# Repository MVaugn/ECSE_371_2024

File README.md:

# ECSE_371_2024
Applied Circuit Design, as taught in Spring of 2024. The last Larry Lab featuring Larry Sears himself!

This page and its contents are for reference only. Learn all you can from these examples, but PLEASE design your own circuits. No cheating >:(

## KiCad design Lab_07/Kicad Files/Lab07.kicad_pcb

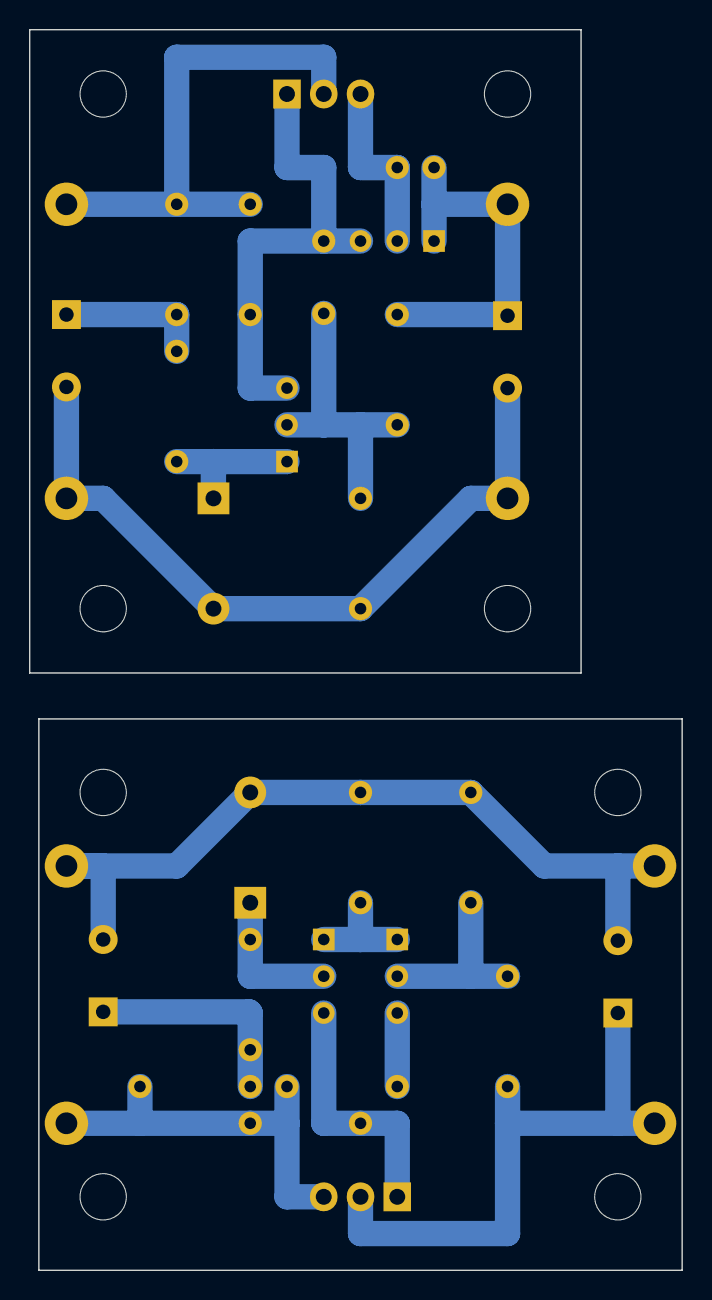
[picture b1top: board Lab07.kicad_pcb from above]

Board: 2 copper layers, 45.1 x 85.7 mm, 34 parts (0 on the bottom side), 16 nets.

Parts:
C101: 22uF; CP_Radial_D10.0mm_P5.00mm
C102: 0.01uF; C_Disc_D10.0mm_W2.5mm_P5.00mm
C103, C302: 100uF; CP_Radial_D10.0mm_P5.00mm
C301: 220uF; CP_Radial_D10.0mm_P5.00mm
D101, D301: 6.2V; D_DO-41_SOD81_P7.62mm_Horizontal
J101, J102, J301, J302: Conn_01x01_Socket; TestPoint_Loop_D2.54mm_Drill1.5mm_Beaded
J103, J304: 0; TestPoint_Loop_D2.54mm_Drill1.5mm_Beaded
J104, J303: Output_Terminal; TestPoint_Loop_D2.54mm_Drill1.5mm_Beaded
Q101, Q103, Q301, Q303: NPN; TO-92L_Inline_Wide
Q102: TIP102; TO-220-3_Vertical
Q302: PMOS; TO-220-3_Vertical
R101, R103, R301, R302: 1K; R_Axial_DIN0207_L6.3mm_D2.5mm_P7.62mm_Horizontal
R102, R106: 2K2; R_Axial_DIN0207_L6.3mm_D2.5mm_P7.62mm_Horizontal
R104: 390m; R_Axial_DIN0207_L6.3mm_D2.5mm_P2.54mm_Vertical
R105: 680R; R_Axial_DIN0207_L6.3mm_D2.5mm_P7.62mm_Horizontal
R303, R304: 100K; R_Axial_DIN0207_L6.3mm_D2.5mm_P7.62mm_Horizontal
R305: 8K2; R_Axial_DIN0207_L6.3mm_D2.5mm_P7.62mm_Horizontal
R306: 1K5; R_Axial_DIN0207_L6.3mm_D2.5mm_P7.62mm_Horizontal
R307: 4K7; R_Axial_DIN0207_L6.3mm_D2.5mm_P7.62mm_Horizontal

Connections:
/Vin_1: J101.1, Q102.2 (C), R101.1, R102.1
/Vin_3: J301.1, Q302.3 (S), R301.1, R303.1, R304.1
/Vout_1: C103.1, J103.1 (In), Q103.1 (E), R104.2, R105.1
/Vout_3: C302.1, J303.1 (In), Q302.2 (D), R306.1
GND: C101.2, C103.2, C301.2, C302.2, D101.2 (A), D301.2 (A), J102.1, J104.1 (In), J302.1, J304.1 (In), R106.2, R305.2, R307.2
unnamed: C101.1, R101.2, R103.1
unnamed: C301.1, R301.2, R302.1
unnamed: D101.1 (K), Q101.1 (E), R103.2
unnamed: D301.1 (K), Q301.2 (B), R302.2
unnamed: C102.2, Q101.2 (B), R105.2, R106.1
unnamed: C102.1, Q101.3 (C), Q102.1 (B), Q103.3 (C), R102.2
unnamed: Q102.3 (E), Q103.2 (B), R104.1
unnamed: Q301.3 (C), Q302.1 (G), R304.2
unnamed: Q301.1 (E), Q303.1 (E), R305.1
unnamed: Q303.2 (B), R306.2, R307.1
unnamed: Q303.3 (C), R303.2

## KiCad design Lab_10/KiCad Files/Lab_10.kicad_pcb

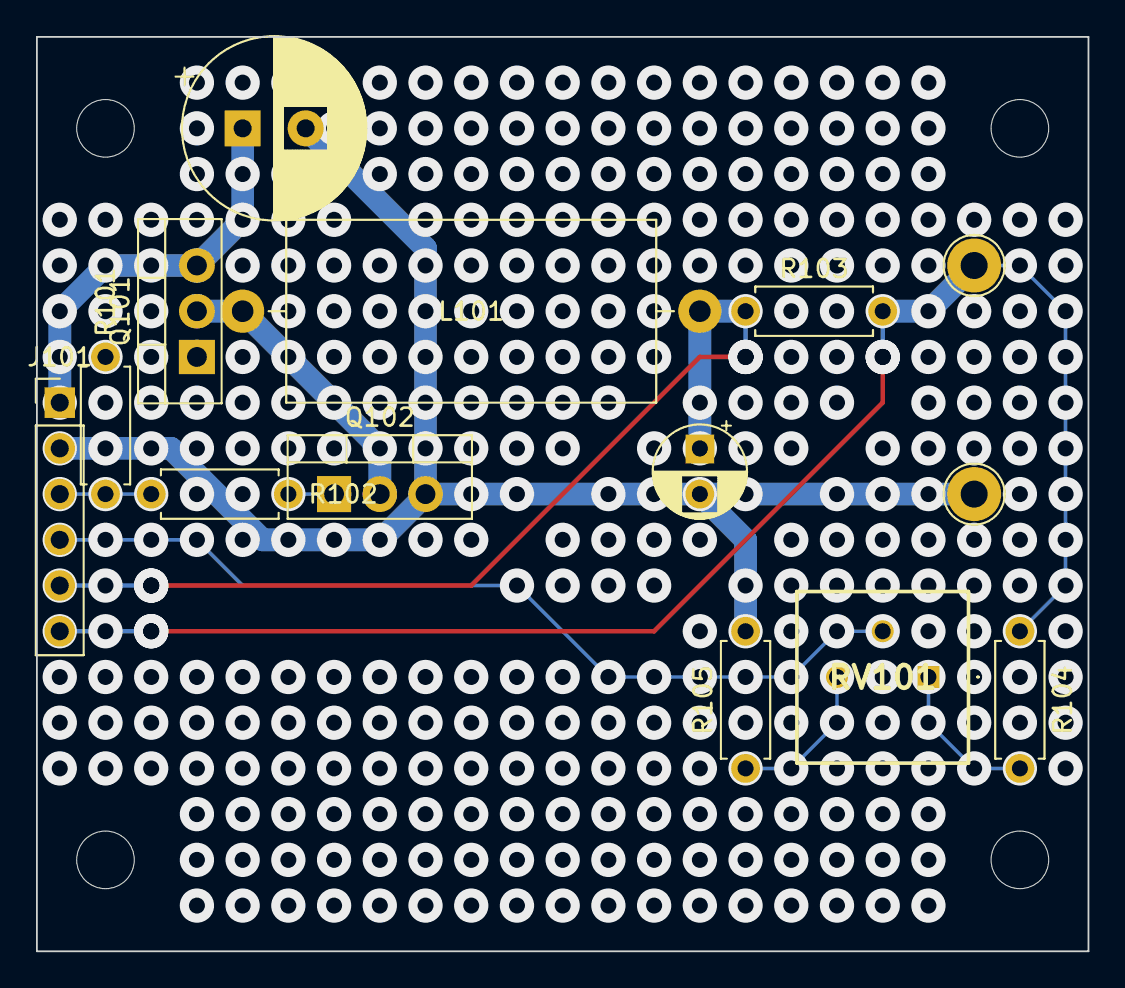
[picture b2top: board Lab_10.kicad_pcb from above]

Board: 2 copper layers, 58.4 x 50.8 mm, 14 parts (0 on the bottom side), 11 nets.

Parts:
C101: 100uF; CP_Radial_D10.0mm_P3.50mm
C102: 10uF; CP_Radial_D5.0mm_P2.50mm
J101: Conn_01x06_Socket; PinHeader_1x06_P2.54mm_Vertical
J102, J103: Output_Terminal; TestPoint_Loop_D2.54mm_Drill1.5mm_Beaded
L101: 820uH; L_Axial_L20.3mm_D12.7mm_P25.40mm_Horizontal_Vishay_IHA-201
Q101: IRF9Z24; TO-220-3_Vertical
Q102: IRF530; TO-220-3_Vertical
R101, R102: 100R; R_Axial_DIN0207_L6.3mm_D2.5mm_P7.62mm_Horizontal
R103: 0.12R; R_Axial_DIN0207_L6.3mm_D2.5mm_P7.62mm_Horizontal
R104: 1K; R_Axial_DIN0207_L6.3mm_D2.5mm_P7.62mm_Horizontal
R105: 27K; R_Axial_DIN0207_L6.3mm_D2.5mm_P7.62mm_Horizontal
RV101: 50K; 3386P1503

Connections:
/GateDrive: J101.3, R101.2, R102.1
/Vfdbk: J101.4, RV101.2
/Vs+: C102.1, J101.5, L101.2, R103.1
/Vs-: J101.6, J103.1 (In), R103.2, R104.1
unnamed: L101.1, Q101.2 (D), Q102.2 (D)
unnamed: Q101.1 (G), R101.1
unnamed: Q102.1 (G), R102.2
unnamed: R104.2, RV101.1
unnamed: R105.1, RV101.3
PGND: C101.2, C102.2, J101.2, J102.1 (In), Q102.3 (S), R105.2
V_Supply: C101.1, J101.1, Q101.3 (S)

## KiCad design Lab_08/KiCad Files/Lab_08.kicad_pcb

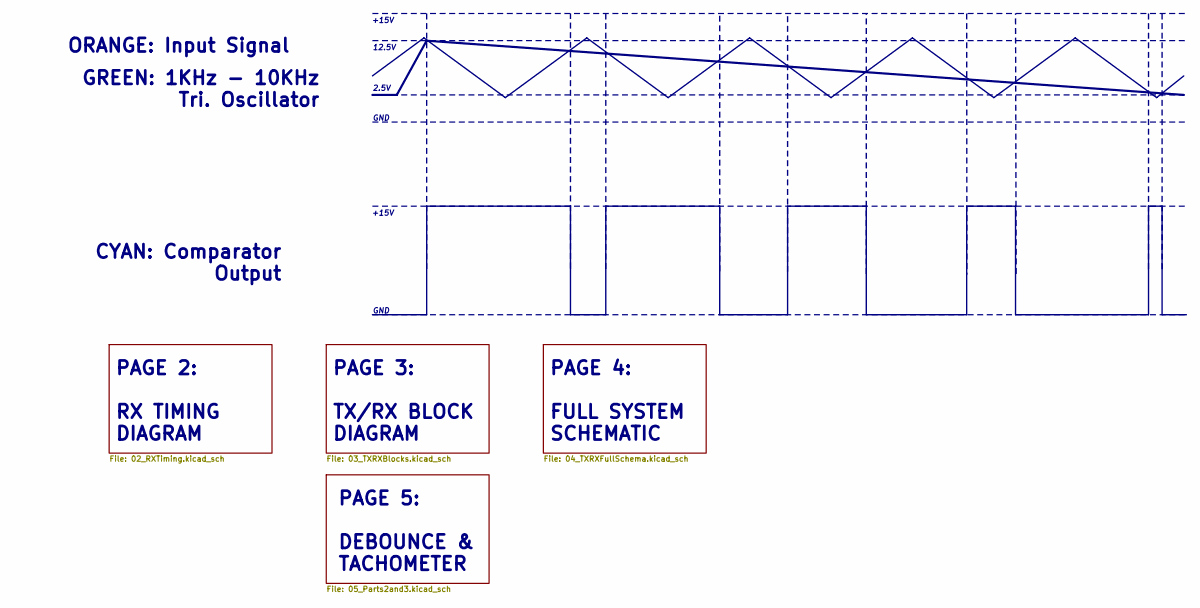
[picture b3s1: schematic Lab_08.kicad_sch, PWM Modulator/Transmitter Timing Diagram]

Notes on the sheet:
PAGE 4: FULL SYSTEM SCHEMATIC
ORANGE: Input Signal
2.5V
GREEN: 1KHz - 10KHz Tri. Oscillator
PAGE 3: TX/RX BLOCK DIAGRAM
CYAN: Comparator Output
+15V
12.5V
PAGE 2: RX TIMING DIAGRAM
GND
PAGE 5: DEBOUNCE & TACHOMETER

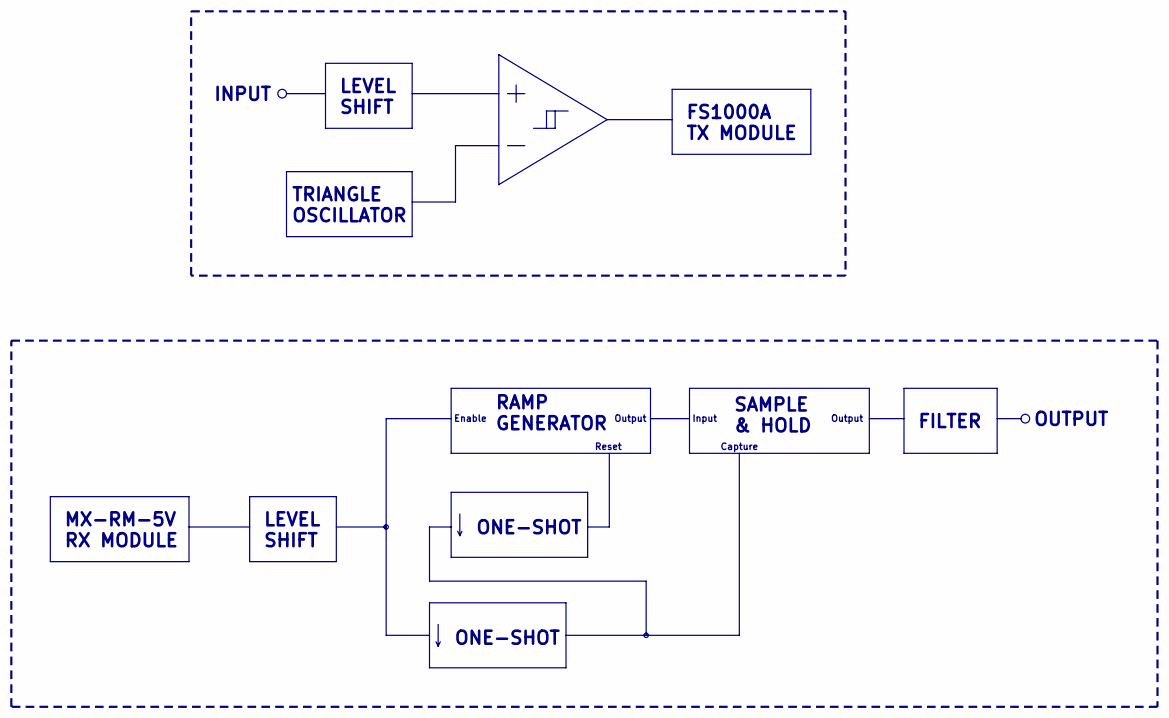
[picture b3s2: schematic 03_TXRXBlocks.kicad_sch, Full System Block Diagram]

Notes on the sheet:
FILTER
Output
Capture
RAMP GENERATOR
ONE-SHOT
LEVEL SHIFT
FS1000A TX MODULE
MX-RM-5V RX MODULE
TRIANGLE OSCILLATOR
Reset
Enable
OUTPUT
INPUT
SAMPLE & HOLD
Input

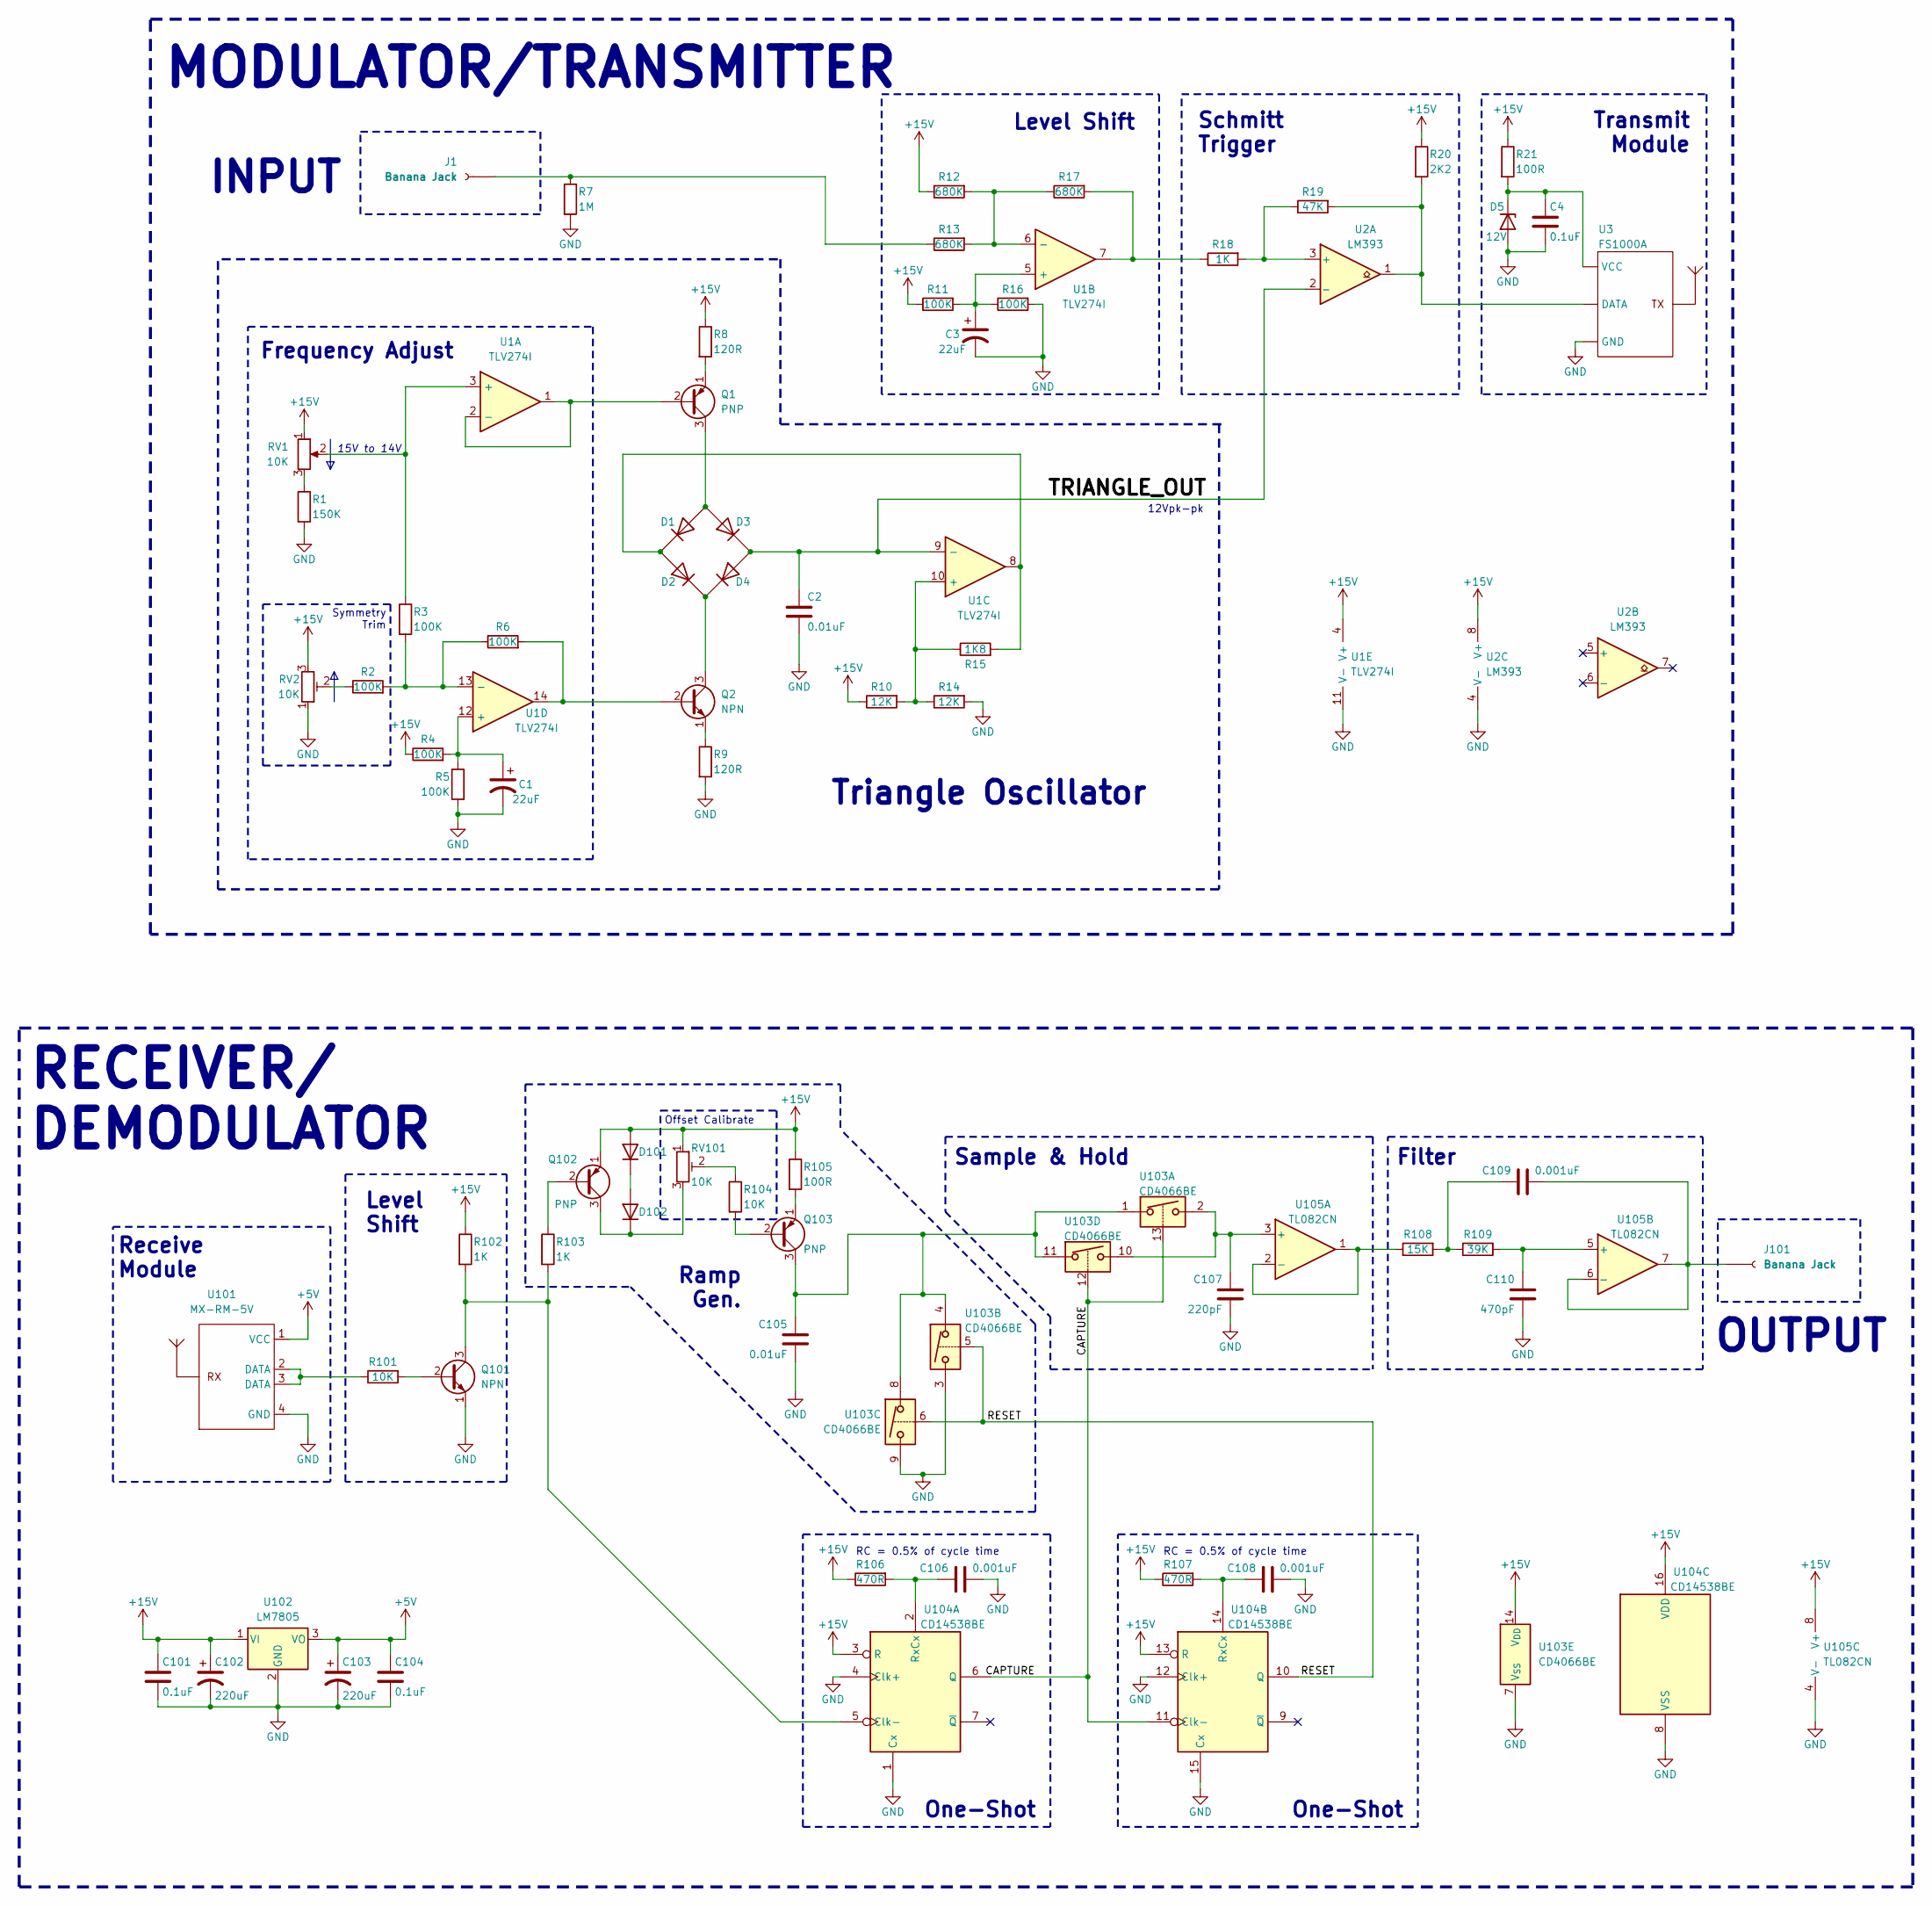
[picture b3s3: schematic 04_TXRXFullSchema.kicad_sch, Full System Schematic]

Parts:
C1, C3: 22uF; CP_Radial_D6.3mm_P2.50mm
C2, C105: 0.01uF; C_Disc_D3.0mm_W1.6mm_P2.50mm
C4, C101, C104: 0.1uF; C_Rect_L11.0mm_W2.8mm_P10.00mm_MKT
C102, C103: 220uF; CP_Radial_D8.0mm_P5.00mm
C106, C108, C109: 0.001uF; C_Disc_D3.0mm_W1.6mm_P2.50mm
C107: 220pF; C_Disc_D3.0mm_W1.6mm_P2.50mm
C110: 470pF; C_Disc_D3.0mm_W1.6mm_P2.50mm
D1, D2, D3, D4: D_A-405_P7.62mm_Horizontal
D5: 12V; D_A-405_P7.62mm_Horizontal
D101, D102: D; D_A-405_P7.62mm_Horizontal
J1, J101: Banana Jack
Q1, Q102, Q103: PNP; TO-92_Inline_Wide
Q2, Q101: NPN; TO-92_Inline_Wide
R1: 150K; R_Axial_DIN0207_L6.3mm_D2.5mm_P10.16mm_Horizontal
R2, R5, R11: 100K; R_Axial_DIN0207_L6.3mm_D2.5mm_P7.62mm_Horizontal
R3, R4, R16: 100K; R_Axial_DIN0207_L6.3mm_D2.5mm_P10.16mm_Horizontal
R6: 100K; R_Axial_DIN0207_L6.3mm_D2.5mm_P5.08mm_Vertical
R7: 1M; R_Axial_DIN0207_L6.3mm_D2.5mm_P10.16mm_Horizontal
R8, R9: 120R; R_Axial_DIN0207_L6.3mm_D2.5mm_P7.62mm_Horizontal
R10, R14: 12K; R_Axial_DIN0207_L6.3mm_D2.5mm_P10.16mm_Horizontal
R12, R13: 680K; R_Axial_DIN0207_L6.3mm_D2.5mm_P7.62mm_Horizontal
R15: 1K8; R_Axial_DIN0207_L6.3mm_D2.5mm_P5.08mm_Vertical
R17: 680K; R_Axial_DIN0207_L6.3mm_D2.5mm_P2.54mm_Vertical
R18, R102, R103: 1K; R_Axial_DIN0207_L6.3mm_D2.5mm_P7.62mm_Horizontal
R19: 47K; R_Axial_DIN0207_L6.3mm_D2.5mm_P5.08mm_Vertical
R20: 2K2; R_Axial_DIN0207_L6.3mm_D2.5mm_P7.62mm_Horizontal
R21, R105: 100R; R_Axial_DIN0207_L6.3mm_D2.5mm_P7.62mm_Horizontal
R101, R104: 10K; R_Axial_DIN0207_L6.3mm_D2.5mm_P7.62mm_Horizontal
R106: 470R; R_Axial_DIN0207_L6.3mm_D2.5mm_P7.62mm_Horizontal
R107: 470R; R_Axial_DIN0207_L6.3mm_D2.5mm_P10.16mm_Horizontal
R108: 15K; R_Axial_DIN0207_L6.3mm_D2.5mm_P7.62mm_Horizontal
R109: 39K; R_Axial_DIN0207_L6.3mm_D2.5mm_P7.62mm_Horizontal
RV1, RV2, RV101: 10K; Potentiometer_ACP_CA9-V10_Vertical
U1: TLV274I; DIP-14_W7.62mm
U2: LM393; DIP-8_W7.62mm
U3: FS1000A; PinHeader_1x03_P2.54mm_Vertical
U101: MX-RM-5V; PinHeader_1x04_P2.54mm_Vertical
U102: LM7805; TO-220-3_Vertical
U103: CD4066BE; DIP-14_W7.62mm
U104: CD14538BE; DIP-16_W7.62mm
U105: TL082CN; DIP-8_W7.62mm

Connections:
+5V: C103.1, C104.1, U101.1 (VCC), U102.3 (VO)
+15V: C101.1, C102.1, D101.2 (A), Q102.1 (E), R4.1, R8.1, R10.1, R11.1, R12.1, R20.1, R21.1, R102.1, R105.1, R106.1, R107.1, RV1.1, RV2.3, RV101.1, U1.4 (V+), U2.8 (V+), U102.1 (VI), U103.14 (V_{DD}), U104.3 (R), U104.13 (R), U104.16 (VDD), U105.8 (V+)
/Full Schematic/CAPTURE: U103.12, U103.13, U104.6 (Q), U104.11 (Clk-)
/Full Schematic/RESET: U103.5, U103.6, U104.10 (Q)
/Full Schematic/TRIANGLE_OUT: C2.1, D3.1 (K), D4.2 (A), U1.9 (-), U2.2 (-)
GND: C1.2, C2.2, C3.2, C4.2, C101.2, C102.2, C103.2, C104.2, C105.2, C106.1, C107.2, C108.1, C110.2, D5.2 (A), Q101.1 (E), R1.2, R5.2, R7.2, R9.2, R14.2, R16.2, RV2.1, U1.11 (V-), U2.4 (V-), U3.3 (GND), U101.4 (GND), U102.2 (GND), U103.3, U103.7 (V_{SS}), U103.9, U104.1 (Cx), U104.4 (Clk+), U104.8 (VSS), U104.12 (Clk+), U104.15 (Cx), U105.4 (V-)
unnamed: C109.2, R108.2, R109.1
unnamed: D1.2 (A), D3.2 (A), Q1.3 (C)
unnamed: D1.1 (K), D2.2 (A), R15.2, U1.8
unnamed: D2.1 (K), D4.1 (K), Q2.3 (C)
unnamed: C4.1, D5.1 (K), R21.2, U3.2 (VCC)
unnamed: D101.1 (K), D102.2 (A)
unnamed: D102.1 (K), Q102.3 (C), RV101.3
unnamed: Q1.2 (B), U1.1, U1.2 (-)
unnamed: Q1.1 (E), R8.2
unnamed: Q2.2 (B), R6.2, U1.14
unnamed: Q2.1 (E), R9.1
unnamed: Q101.2 (B), R101.2
unnamed: Q101.3 (C), R102.2, R103.2, U104.5 (Clk-)
unnamed: Q102.2 (B), R103.1
unnamed: Q103.2 (B), R104.2
unnamed: C105.1, Q103.3 (C), U103.1, U103.4, U103.8, U103.11
unnamed: Q103.1 (E), R105.2
unnamed: R1.1, RV1.3
unnamed: R2.1, RV2.2
unnamed: R7.1, R13.1
unnamed: R17.2, R18.1, U1.7
unnamed: R101.1, U101.2 (DATA), U101.3 (DATA)
unnamed: R104.1, RV101.2
unnamed: R3.1, RV1.2, U1.3 (+)
unnamed: C3.1, R11.2, R16.1, U1.5 (+)
unnamed: R12.2, R13.2, R17.1, U1.6 (-)
unnamed: R10.2, R14.1, R15.1, U1.10 (+)
unnamed: C1.1, R4.2, R5.1, U1.12 (+)
unnamed: R2.2, R3.2, R6.1, U1.13 (-)
unnamed: R18.2, R19.1, U2.3 (+)
unnamed: R19.2, R20.2, U2.1, U3.1 (DATA)
unnamed: C106.2, R106.2, U104.2 (RxCx)
unnamed: C108.2, R107.2, U104.14 (RxCx)
unnamed: C107.1, U103.2, U103.10, U105.3 (+)
unnamed: R108.1, U105.1, U105.2 (-)
unnamed: C110.1, R109.2, U105.5 (+)
unnamed: C109.1, J101.1, U105.6 (-), U105.7

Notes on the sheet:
Level Shift
RECEIVER/ DEMODULATOR
INPUT
Triangle Oscillator
Schmitt Trigger
One-Shot
Sample & Hold
Ramp Gen.
OUTPUT
12Vpk-pk
MODULATOR/TRANSMITTER
Frequency Adjust
Receive Module
15V to 14V
RC = 0.5% of cycle time
Symmetry Trim
Transmit Module
Level Shift
Offset Calibrate
Filter

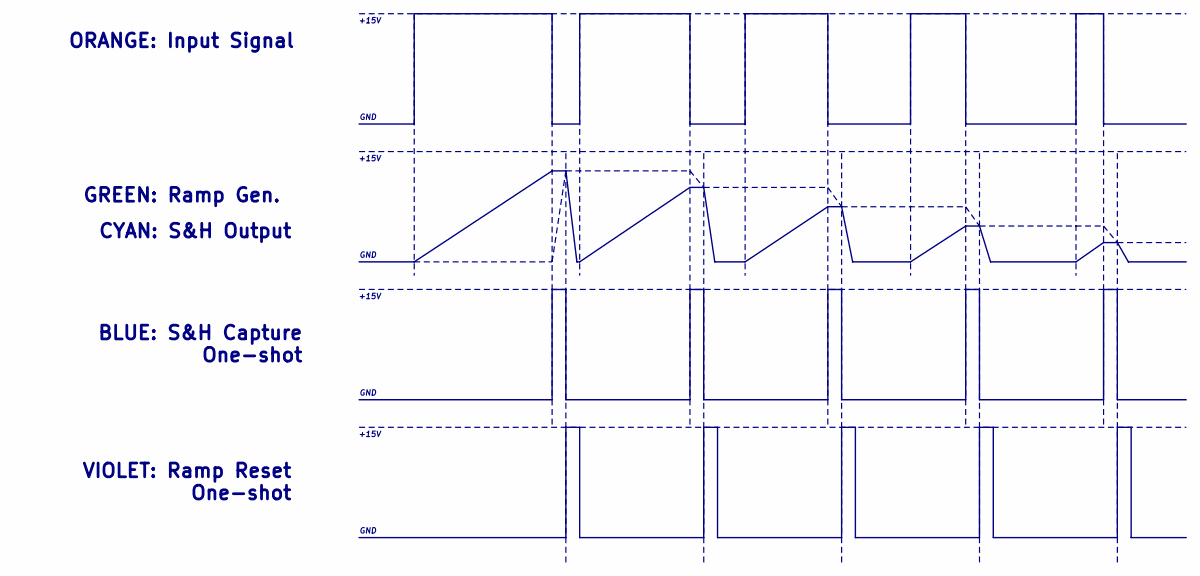
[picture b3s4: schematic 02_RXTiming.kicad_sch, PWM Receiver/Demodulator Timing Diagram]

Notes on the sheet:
CYAN: S&H Output
+15V
BLUE: S&H Capture One-shot
GND
GREEN: Ramp Gen.
VIOLET: Ramp Reset One-shot
ORANGE: Input Signal

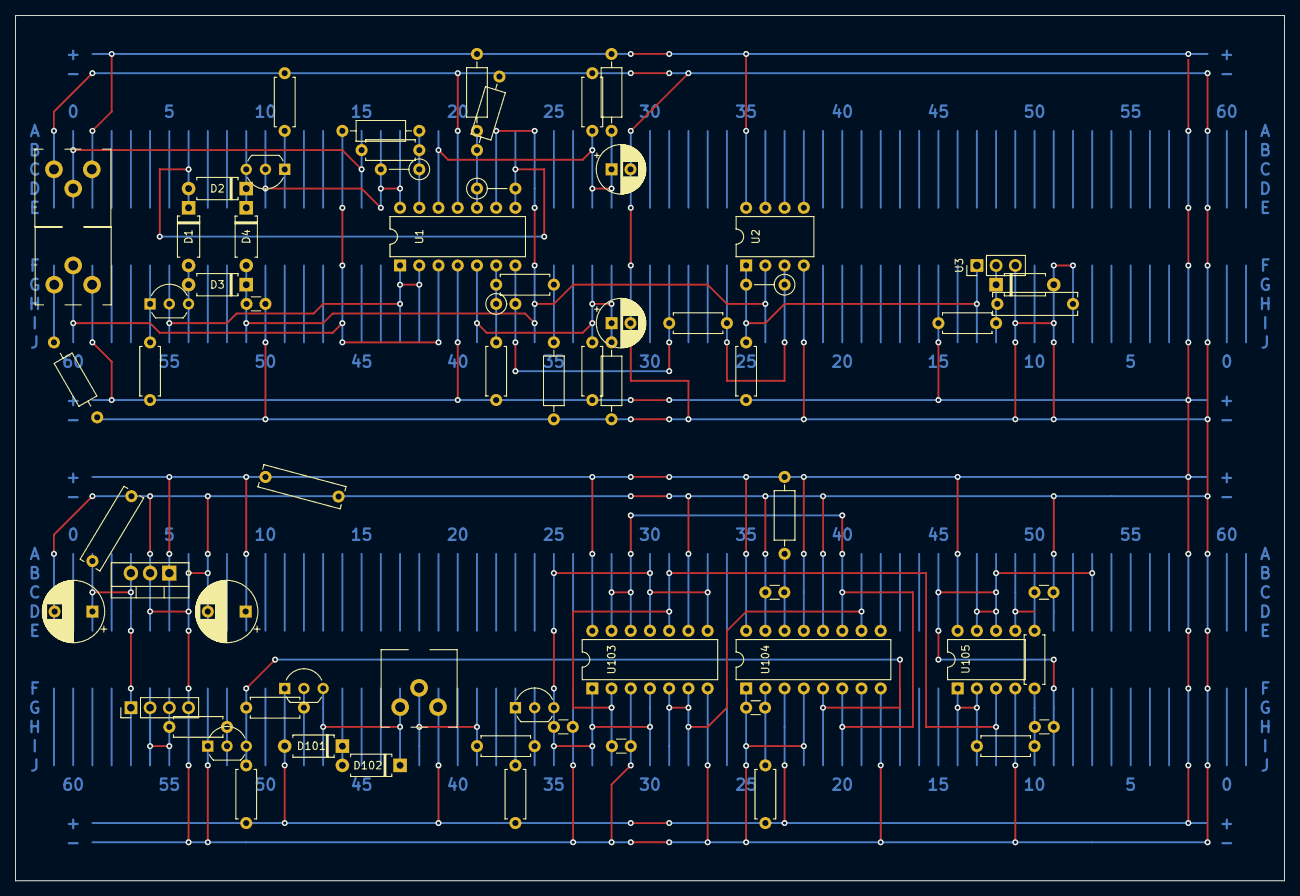
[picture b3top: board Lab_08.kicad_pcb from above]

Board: 2 copper layers, 167.6 x 114.3 mm, 67 parts (0 on the bottom side), 43 nets.

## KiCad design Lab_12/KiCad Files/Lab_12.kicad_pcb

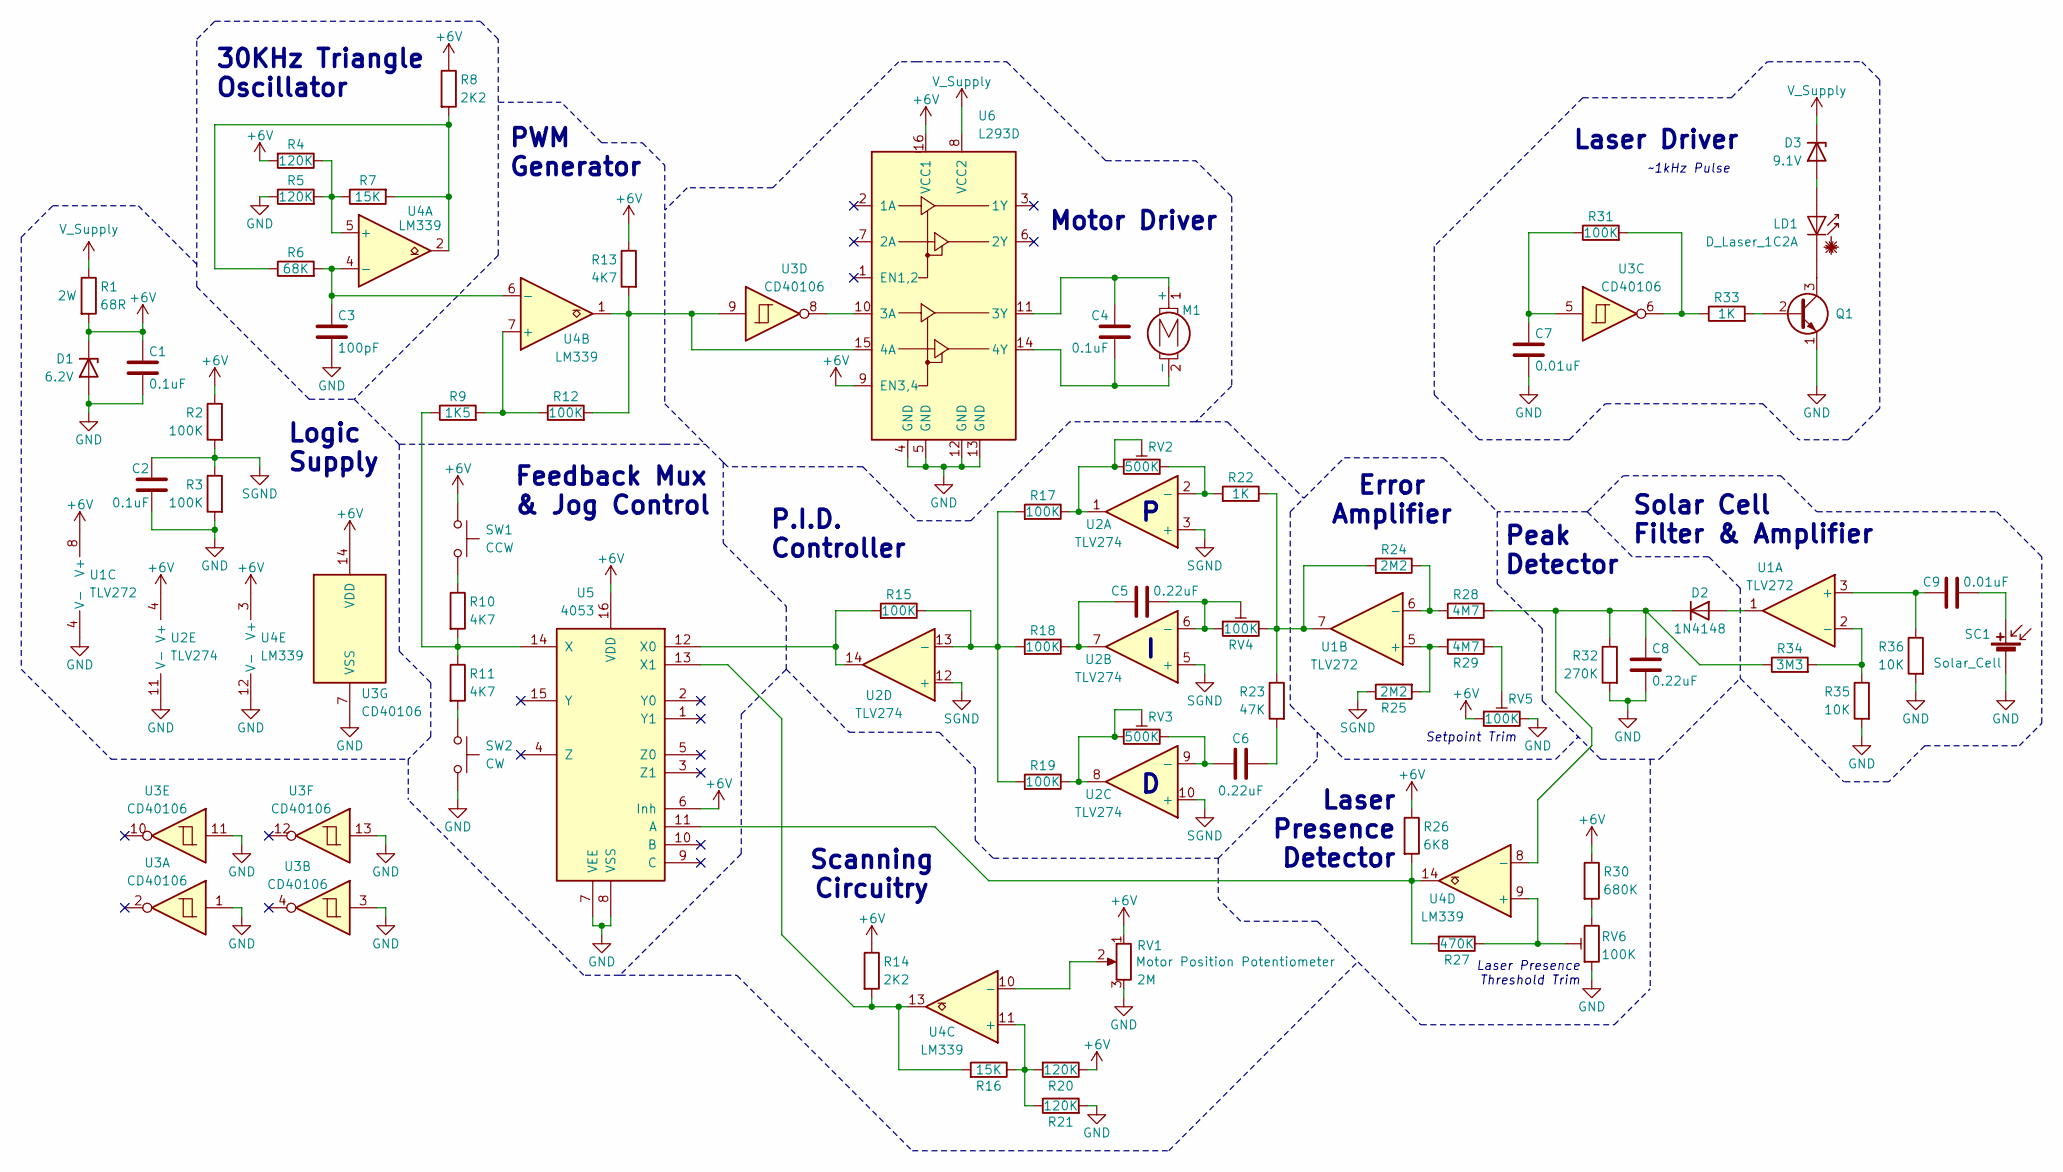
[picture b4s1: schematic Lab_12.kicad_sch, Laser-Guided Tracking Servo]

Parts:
C1, C2, C4: 0.1uF; C_Rect_L16.5mm_W4.7mm_P15.00mm_MKT
C3: 100pF; C_Disc_D9.0mm_W2.5mm_P5.00mm
C5, C6: 0.22uF; C_Disc_D9.0mm_W2.5mm_P5.00mm
C7: 0.01uF; C_Disc_D9.0mm_W5.0mm_P10.00mm
C8: 0.22uF; C_Disc_D9.0mm_W5.0mm_P7.50mm
C9: 0.01uF; C_Disc_D9.0mm_W2.5mm_P5.00mm
D1: 6.2V; D_A-405_P7.62mm_Horizontal
D2: 1N4148; D_A-405_P2.54mm_Vertical_AnodeUp
D3: 9.1V; D_A-405_P12.70mm_Horizontal
LD1: D_Laser_1C2A; PinHeader_1x02_P2.54mm_Vertical
M1: DC Motor; PinHeader_1x02_P2.54mm_Vertical
Q1: 2N4401; TO-92L_Inline_Wide
R1: 68R; R_Axial_DIN0207_L6.3mm_D2.5mm_P7.62mm_Horizontal
R2: 100K; R_Axial_DIN0207_L6.3mm_D2.5mm_P7.62mm_Horizontal
R3: 100K; R_Axial_DIN0207_L6.3mm_D2.5mm_P10.16mm_Horizontal
R4: 120K; R_Axial_DIN0207_L6.3mm_D2.5mm_P7.62mm_Horizontal
R5, R20, R21: 120K; R_Axial_DIN0207_L6.3mm_D2.5mm_P10.16mm_Horizontal
R6: 68K; R_Axial_DIN0207_L6.3mm_D2.5mm_P5.08mm_Vertical
R7: 15K; R_Axial_DIN0207_L6.3mm_D2.5mm_P7.62mm_Horizontal
R8: 2K2; R_Axial_DIN0207_L6.3mm_D2.5mm_P7.62mm_Horizontal
R9: 1K5; R_Axial_DIN0207_L6.3mm_D2.5mm_P7.62mm_Horizontal
R10, R11: 4K7; R_Axial_DIN0207_L6.3mm_D2.5mm_P7.62mm_Horizontal
R12: 100K; R_Axial_DIN0207_L6.3mm_D2.5mm_P5.08mm_Vertical
R13: 4K7; R_Axial_DIN0207_L6.3mm_D2.5mm_P10.16mm_Horizontal
R14: 2K2; R_Axial_DIN0207_L6.3mm_D2.5mm_P10.16mm_Horizontal
R15, R17, R18, R31: 100K; R_Axial_DIN0207_L6.3mm_D2.5mm_P2.54mm_Vertical
R16: 15K; R_Axial_DIN0207_L6.3mm_D2.5mm_P5.08mm_Vertical
R19: 100K; R_Axial_DIN0207_L6.3mm_D2.5mm_P15.24mm_Horizontal
R22: 1K; R_Axial_DIN0207_L6.3mm_D2.5mm_P7.62mm_Horizontal
R23: 47K; R_Axial_DIN0207_L6.3mm_D2.5mm_P2.54mm_Vertical
R24: 2M2; R_Axial_DIN0207_L6.3mm_D2.5mm_P2.54mm_Vertical
R25: 2M2; R_Axial_DIN0207_L6.3mm_D2.5mm_P15.24mm_Horizontal
R26: 6K8; R_Axial_DIN0207_L6.3mm_D2.5mm_P10.16mm_Horizontal
R27: 470K; R_Axial_DIN0207_L6.3mm_D2.5mm_P15.24mm_Horizontal
R28, R29: 4M7; R_Axial_DIN0207_L6.3mm_D2.5mm_P7.62mm_Horizontal
R30: 680K; R_Axial_DIN0207_L6.3mm_D2.5mm_P10.16mm_Horizontal
R32: 270K; R_Axial_DIN0207_L6.3mm_D2.5mm_P7.62mm_Horizontal
R33: 1K; R_Axial_DIN0207_L6.3mm_D2.5mm_P5.08mm_Vertical
R34: 3M3; R_Axial_DIN0207_L6.3mm_D2.5mm_P5.08mm_Vertical
R35, R36: 10K; R_Axial_DIN0207_L6.3mm_D2.5mm_P10.16mm_Horizontal
RV1: 2M; PinHeader_1x03_P2.54mm_Vertical
RV2, RV3: 500K; 3386P1503
RV4, RV5, RV6: 100K; 3386P1503
SC1: Solar_Cell; PinHeader_1x02_P2.54mm_Vertical
SW1: CCW; SW_PUSH_6mm_H9.5mm
SW2: CW; SW_PUSH_6mm_H9.5mm
U1: TLV272; DIP-8_W7.62mm
U2: TLV274; DIP-14_W7.62mm
U3: CD40106; DIP-14_W7.62mm
U4: LM339; DIP-14_W7.62mm
U5: 4053; DIP-16_W7.62mm
U6: L293D; DIP-16_W7.62mm

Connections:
+6V: C1.1, D1.1 (K), R1.2, R2.1, R4.2, R8.1, R13.1, R14.1, R20.1, R26.1, R30.1, RV1.1, RV5.1, SW1.2, U1.8 (V+), U2.4 (V+), U3.14 (VDD), U4.3 (V+), U5.6 (Inh), U5.16 (VDD), U6.9 (EN3,4), U6.16 (VCC1)
GND: C1.2, C2.2, C3.2, C7.2, C8.2, D1.2 (A), Q1.1 (E), R3.2, R5.1, R21.2, R32.2, R35.2, R36.2, RV1.3, RV5.3, RV6.1, SC1.2 (-), SW2.1, U1.4 (V-), U2.11 (V-), U3.1, U3.3, U3.7 (VSS), U3.11, U3.13, U4.12 (V-), U5.7 (VEE), U5.8 (VSS), U6.4 (GND), U6.5 (GND), U6.12 (GND), U6.13 (GND)
unnamed: C5.2, R18.1, U2.7
unnamed: C6.1, R23.2
unnamed: C7.1, R31.1, U3.5
unnamed: D2.2 (A), U1.1
unnamed: C8.1, D2.1 (K), R28.1, R32.1, R34.1, U4.8 (-)
unnamed: D3.2 (A), LD1.2 (A)
unnamed: LD1.1 (K), Q1.3 (C)
unnamed: C4.1, M1.1 (+), U6.11 (3Y)
unnamed: C4.2, M1.2 (-), U6.14 (4Y)
unnamed: Q1.2 (B), R33.2
unnamed: R6.1, R7.2, R8.2, U4.2
unnamed: R10.1, SW1.1
unnamed: R11.2, SW2.2
unnamed: R17.1, RV2.1, RV2.2, U2.1
unnamed: R19.1, RV3.1, RV3.2, U2.8
unnamed: R22.1, R23.1, R24.2, RV4.3, U1.7
unnamed: R29.1, RV5.2
unnamed: R30.2, RV6.3
unnamed: R31.2, R33.1, U3.6
unnamed: C9.1, SC1.1 (+)
unnamed: C9.2, R36.1, U1.3 (+)
unnamed: R34.2, R35.1, U1.2 (-)
unnamed: R25.2, R29.2, U1.5 (+)
unnamed: R24.1, R28.2, U1.6 (-)
unnamed: R22.2, RV2.3, U2.2 (-)
unnamed: C5.1, RV4.1, RV4.2, U2.6 (-)
unnamed: C6.2, RV3.3, U2.9 (-)
unnamed: R15.1, R17.2, R18.2, R19.2, U2.13 (-)
unnamed: R4.1, R5.2, R7.1, U4.5 (+)
unnamed: C3.1, R6.2, U4.4 (-), U4.6 (-)
unnamed: R9.2, R12.1, U4.7 (+)
unnamed: R16.1, R20.2, R21.1, U4.11 (+)
unnamed: RV1.2, U4.10 (-)
unnamed: R27.1, RV6.2, U4.9 (+)
unnamed: R26.2, R27.2, U4.14, U5.11 (A)
unnamed: R15.2, U2.14, U5.12 (X0)
unnamed: R14.2, R16.2, U4.13, U5.13 (X1)
unnamed: R9.1, R10.2, R11.1, U5.14 (X)
unnamed: U3.8, U6.10 (3A)
unnamed: R12.2, R13.2, U3.9, U4.1, U6.15 (4A)
SGND: C2.1, R2.2, R3.1, R25.1, U2.3 (+), U2.5 (+), U2.10 (+), U2.12 (+)
V_Supply: D3.1 (K), R1.1, U6.8 (VCC2)

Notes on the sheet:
Logic Supply
Motor Driver
Laser Presence Threshold Trim
Laser Presence Detector
Solar Cell Filter & Amplifier
Peak Detector
~1kHz Pulse
P.I.D. Controller
Error Amplifier
Laser Driver
Setpoint Trim
30KHz Triangle Oscillator
Scanning Circuitry
PWM Generator
Feedback Mux & Jog Control

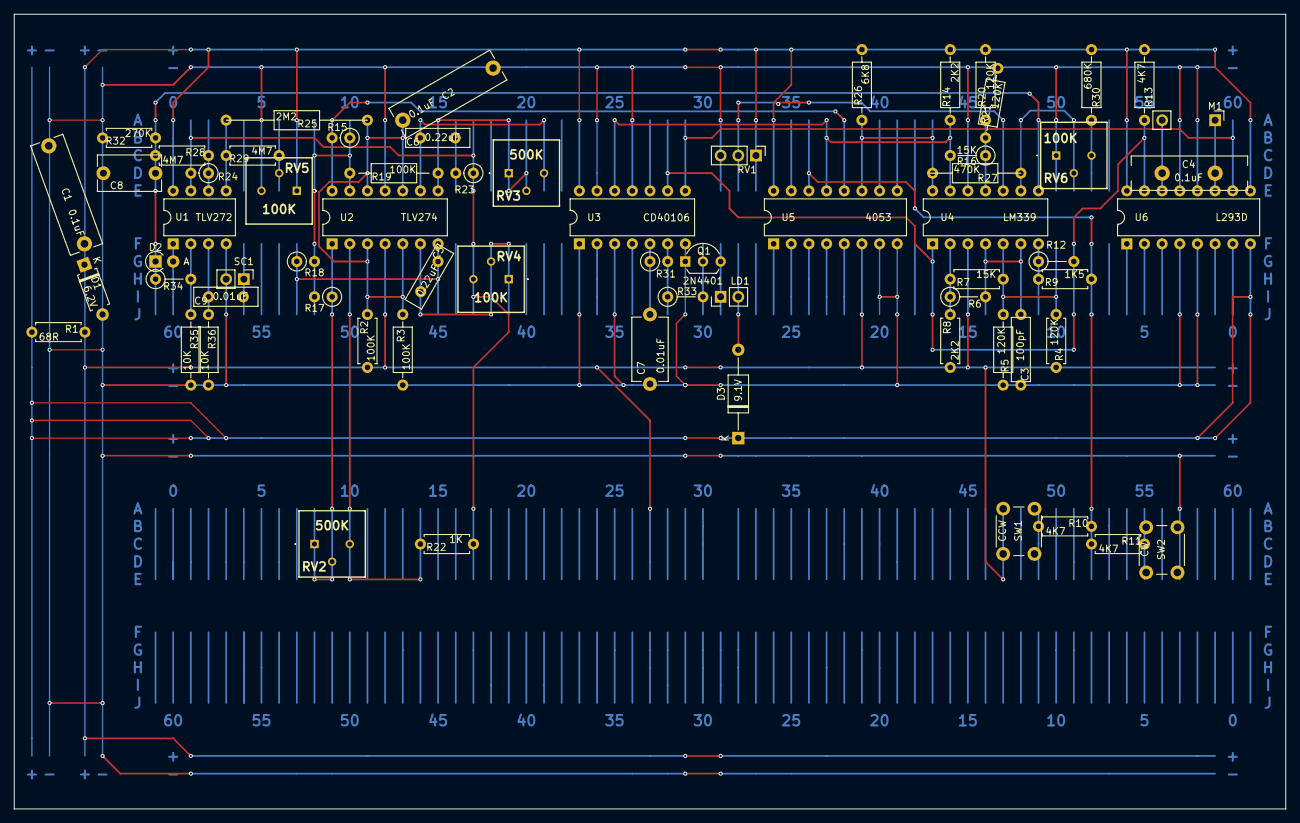
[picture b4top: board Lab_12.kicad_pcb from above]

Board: 2 copper layers, 182.9 x 114.3 mm, 66 parts (0 on the bottom side), 44 nets.

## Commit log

2024-01-16 Organize KiCAD Projects
2024-01-16 Create Report Doc for Lab 01
2024-01-17 lab 0 pics
2024-01-17 Create PDF slides for Lab 01
2024-01-17 markdown writeup made
2024-01-17 writeup outline
2024-01-17 5-11 finished
2024-01-17 Outline first half of lab 01
2024-01-17 Edit lab 01 formatting
2024-01-17 test
2024-01-17 Edit lab 1 writeup formatting
2024-01-19 Simulate Lab 1 Problem 5
2024-01-20 Edit Lab01 P5 Simulation
2024-01-20 Capture and simulate P6&7 schemas
2024-01-20 final lab1 sat sch
2024-01-23 through q5 done
2024-01-24 Update RC Filters
2024-01-24 Edit Answers
2024-01-24 Edit up to Question 9
2024-01-25 Simulate Problem 8
2024-01-25 Update Lab 01 Problem 8 schematic
2024-01-25 Finish Lab 01
2024-01-25 almost done. need 2 more imgs
2024-01-26 Add Op-Amp Lecture
2024-01-26 lab 2 init
2024-01-26 q4 ss done
2024-01-27 Organize Saturday Schematic Sheets
2024-01-27 Add Lab 02 PDF
2024-01-27 Finish Lab 02 Saturday Schematics
2024-01-27 writeup
2024-02-02 Finish Lab 02
2024-02-02 Add writeup doc
2024-02-03 lab 3 init
2024-02-03 1 done
2024-02-03 Start Problem 2
2024-02-03 bugfix;
2024-02-03 Finish Schematics & Scope traces through part 2
2024-02-05 markey push
2024-02-05 Add Helpful Datasheets
2024-02-05 Stash possible circuit topology in subsheet
2024-02-05 tweaks
2024-02-05 Update earlier parts of lab03
2024-02-05 Update part 3
2024-02-06 output stage
2024-02-06 Complete first revision lab 3 Schematic
2024-02-08 final lab3
2024-02-08 Finalize Lab 3 Post-Recitation
2024-02-13 Add Lab 4 Part 1D and 1E
2024-02-13 123 done
2024-02-15 push
2024-02-15 Finish Lab 4
2024-02-16 initial commit lab5
2024-02-17 Reorganize Lab 5
2024-02-17 Continue Lab 5
2024-02-17 Finish Saturday Schematics
2024-02-20 Revise part 3 Version 1
    For next revision:
    - add collector resistor to Q304
    - remove R309
    - add emitter follower after integrator
    For the future:
    - add more poles to bandpass!!
2024-02-20 Annotate Part 3
2024-02-22 Finish Lab 5
2024-02-23 Add Lab 6 Description
2024-02-23 Reorganize Kicad
2024-02-23 Create Hierarchical Sheets
2024-02-24 Begin Saturday Schematic
2024-02-24 Continue Lab 6 Saturday Schematic
2024-02-25 Finish Saturday Schematic
2024-02-25 Revise Schematic
2024-02-25 Add more helpful datasheets
2024-02-27 Finish Revision 2 Schematic
2024-02-27 Move things around
2024-03-02 Complete Revision 3 Lab 6 Schematic
2024-03-02 Reorganize Lab 7
2024-03-03 Finish Lab 7 Saturday Schematic
2024-03-03 Add Connecting Line For Selector Switch
2024-03-05 Revise Lab 7 Schematic
2024-03-07 Finish Lab 7
2024-03-07 Submit Labs 6 & 7
2024-03-15 Start Lab 8
2024-03-18 Continue Lab 8
2024-03-18 Add Pin labels to darlington datasheet
2024-03-18 Complete Lab 8 First Revision Schema
2024-03-19 Annotate Part 1 Schematic
2024-03-23 Finish Lab 8
2024-03-25 Continue Lab 9
2024-03-31 Finish Lab 9
2024-03-31 Upload Labs 10 & 11
2024-04-03 Continue Lab 10
2024-04-05 Finish Lab 10 Schematic
2024-04-06 Complete Lab 10
2024-04-07 Complete Lab 11 Saturday Schematic
2024-04-08 Complete Revision 1 of Lab 11
2024-04-09 Continue Lab 11 Schematic
2024-04-10 Lab 11 Revision 3 Update
2024-04-11 Lab 11 Revision 4
2024-04-19 Finalize lab 11, add labs 12 & 13
2024-04-30 Continue Lab 12 Version 0
2024-04-30 Continue Lab 12
2024-05-06 Continue Lab 12 Schema
2024-05-06 Finish Lab 12 Schema Rev1
2024-05-06 Begin Lab 12 Breadboard Layout
2024-05-07 Finish Lab 12 Breadboard Layout
2024-05-07 Connect Unused 40106 Inputs to GND
2024-05-09 Finish Lab 12
2024-05-09 Finish Lab 13 Schema
2024-12-12 Update Files for KiCad 8
2024-12-12 Plot pdf version of final Lab 11 Schematic
